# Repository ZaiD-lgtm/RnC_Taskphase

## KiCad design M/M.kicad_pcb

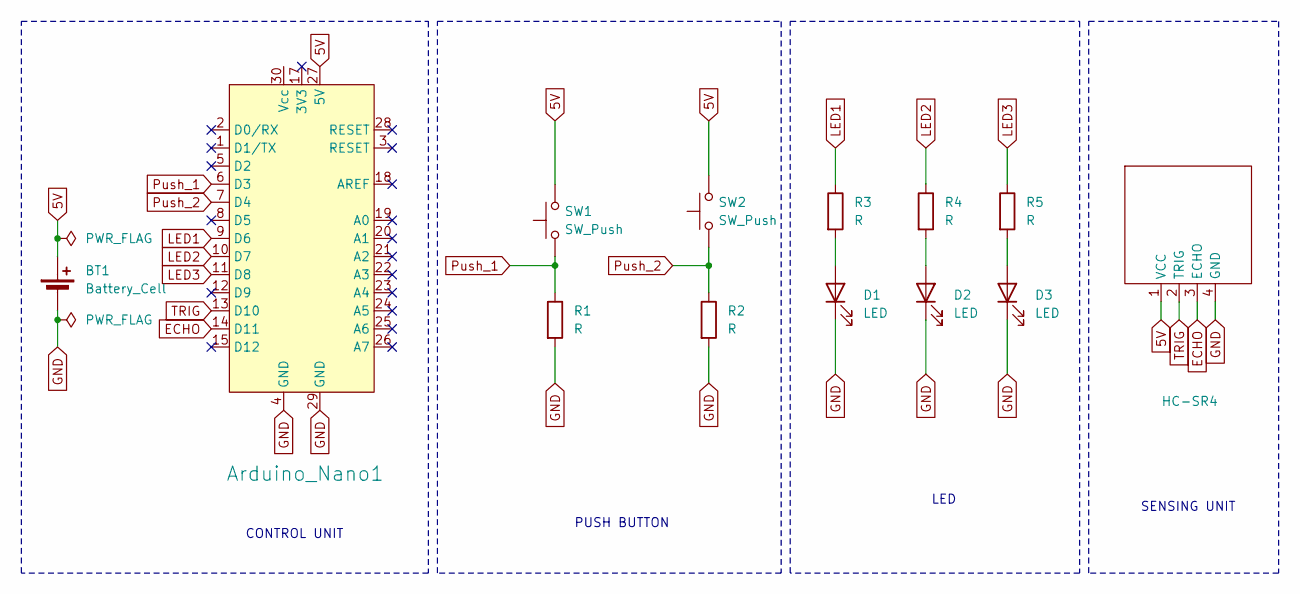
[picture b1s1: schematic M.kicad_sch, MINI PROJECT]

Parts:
Arduino_Nano1: Arduino_Nano_C
BT1: Battery_Cell
D1, D2, D3: LED; LED_D5.0mm
HC-SR4: HC-SR04_C
R1, R2, R3, R4, R5: R; R_Axial_DIN0207_L6.3mm_D2.5mm_P15.24mm_Horizontal
SW1, SW2: SW_Push; SW_PUSH_6mm_H5mm

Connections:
5V: Arduino_Nano1.27 (5V), BT1.1 (+), HC-SR4.1 (VCC), SW1.2, SW2.2
ECHO: Arduino_Nano1.14 (D11), HC-SR4.3 (ECHO)
GND: Arduino_Nano1.4 (GND), Arduino_Nano1.29 (GND), BT1.2 (-), D1.1 (K), D2.1 (K), D3.1 (K), HC-SR4.4 (GND), R1.2, R2.2
LED1: Arduino_Nano1.9 (D6), R3.1
LED2: Arduino_Nano1.10 (D7), R4.1
LED3: Arduino_Nano1.11 (D8), R5.1
unnamed: D1.2 (A), R3.2
unnamed: D2.2 (A), R4.2
unnamed: D3.2 (A), R5.2
Push_1: Arduino_Nano1.6 (D3), R1.1, SW1.1
Push_2: Arduino_Nano1.7 (D4), R2.1, SW2.1
TRIG: Arduino_Nano1.13 (D10), HC-SR4.2 (TRIG)

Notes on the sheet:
CONTROL UNIT
PUSH BUTTON
SENSING UNIT
LED

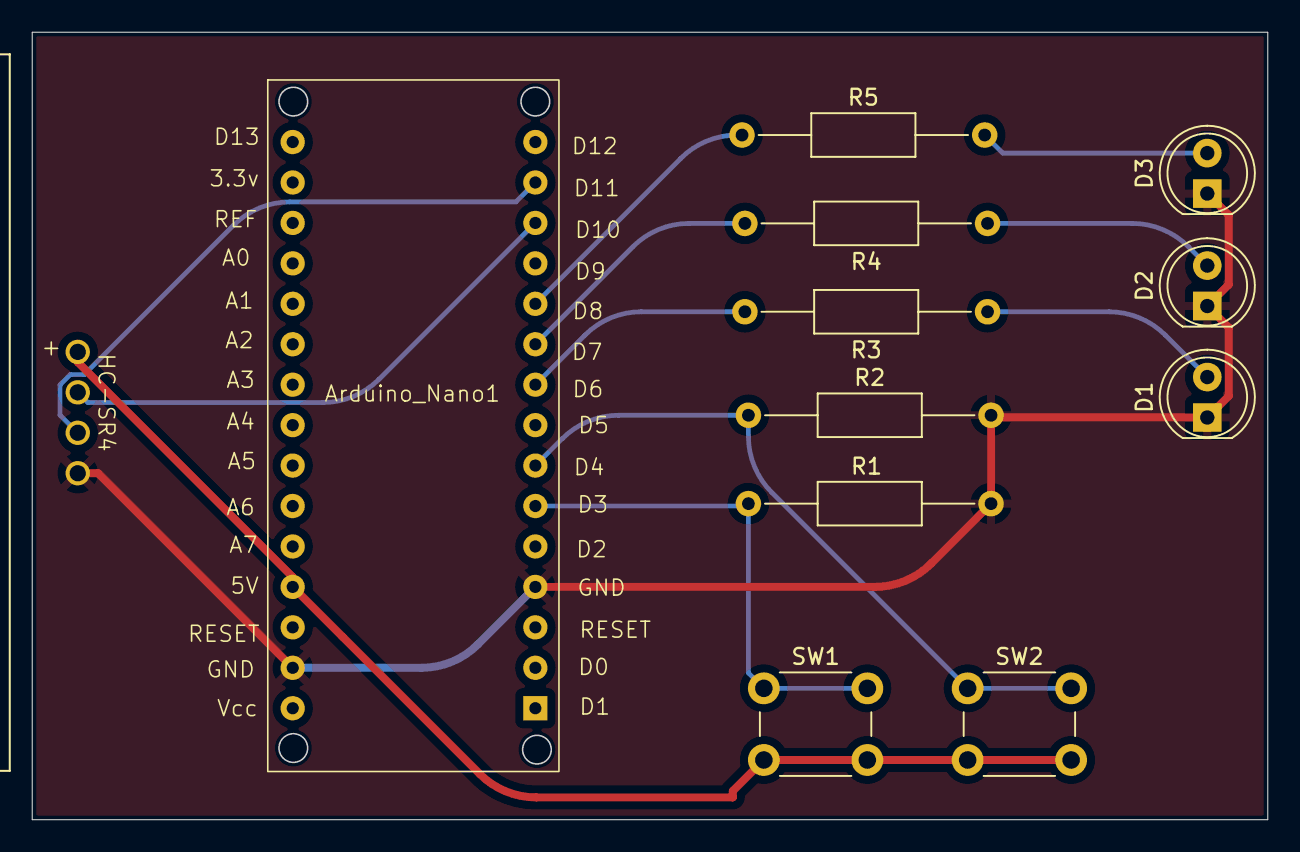
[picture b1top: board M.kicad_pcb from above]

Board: 2 copper layers, 77.5 x 49.4 mm, 12 parts (0 on the bottom side), 12 nets.

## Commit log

2024-12-16 task 2
